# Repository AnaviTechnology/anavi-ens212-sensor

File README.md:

# ANAVI ENS212 Sensor

Open source hardware ENS212 temperature and humidity I2C module.

ANAVI ENS212 Sensor has been designed with [the cross platform and open source electronics design automation suite KiCad](https://kicad.org/).

# License

The project is released under the [Creative Commons Attribution-ShareAlike 4.0 International (CC BY-SA 4.0)](https://creativecommons.org/licenses/by-sa/4.0/).

Note: This is a human-readable summary of (and not a substitute for) the [license](https://creativecommons.org/licenses/by-sa/4.0/legalcode).

You are free to:

Share — copy and redistribute the material in any medium or format Adapt — remix, transform, and build upon the material for any purpose, even commercially. The licensor cannot revoke these freedoms as long as you follow the license terms. Under the following terms:

Attribution — You must give appropriate credit, provide a link to the license, and indicate if changes were made. You may do so in any reasonable manner, but not in any way that suggests the licensor endorses you or your use. ShareAlike — If you remix, transform, or build upon the material, you must distribute your contributions under the same license as the original. No additional restrictions — You may not apply legal terms or technological measures that legally restrict others from doing anything the license permits. Notices:

You do not have to comply with the license for elements of the material in the public domain or where your use is permitted by an applicable exception or limitation. No warranties are given. The license may not give you all of the permissions necessary for your intended use. For example, other rights such as publicity, privacy, or moral rights may limit how you use the material.

You will have to provide a link to the original creator of the project http://www.anavi.technology on any documentation or website.

Credit can be attributed through a link to the creator website: http://www.anavi.technology

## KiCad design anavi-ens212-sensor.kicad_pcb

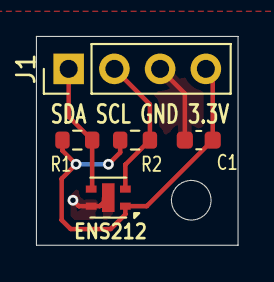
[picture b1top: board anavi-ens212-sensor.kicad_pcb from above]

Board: 2 copper layers, 11.2 x 11.6 mm, 6 parts (0 on the bottom side), 4 nets.

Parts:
C1: 100nF; C_0603_1608Metric
J1: Conn_01x04_Pin; PinHeader_1x04_P2.54mm_Vertical
M: MountingHole_2.2mm_M2
R1, R2: 1kΩ; R_0603_1608Metric
U1: ENS210; AMS_QFN-4-1EP_2x2mm_P0.95mm_EP0.7x1.6mm

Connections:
+3.3V: C1.1, J1.4, R1.1, R2.1, U1.1 (VDD)
GND: C1.2, J1.3, U1.4 (GND), U1.5 (GND)
unnamed: J1.1, R1.2, U1.3 (SDA)
unnamed: J1.2, R2.2, U1.2 (SCL)
